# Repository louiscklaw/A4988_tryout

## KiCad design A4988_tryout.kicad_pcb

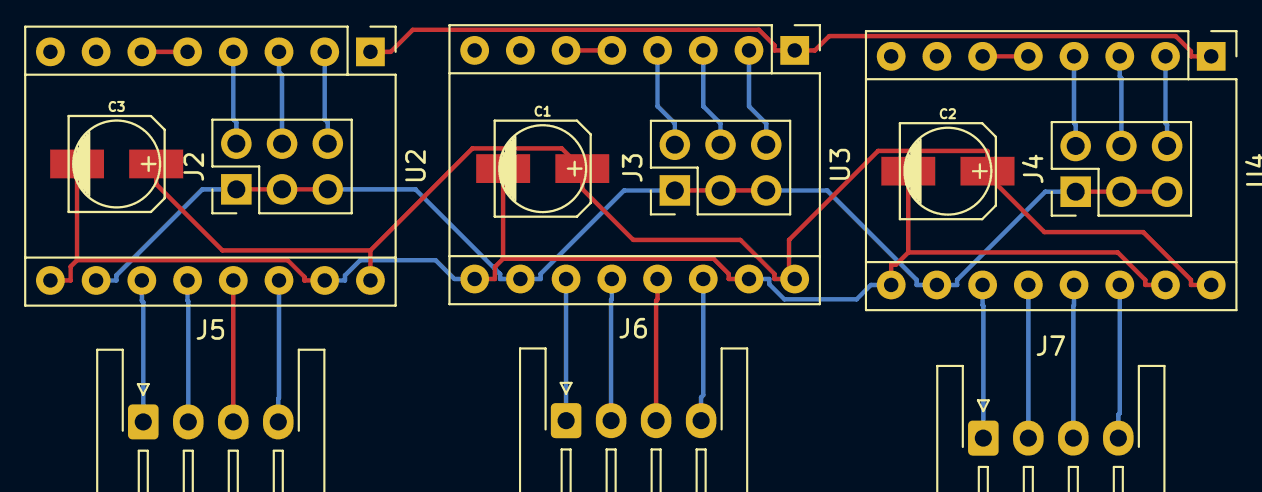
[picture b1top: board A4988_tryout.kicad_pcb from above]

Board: 2 copper layers, 12 parts (0 on the bottom side), 28 nets.

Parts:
C1, C2, C3: CP47uf,35V; c_elec_5x5.3
J2, J3, J4: Conn_02x03_Odd_Even; PinHeader_2x03_P2.54mm_Vertical
J5, J6, J7: Conn_01x04; JST_XH_S04B-XH-A-1_1x04_P2.50mm_Horizontal
U2, U3, U4: A4988_MODULE; Pololu_Breakout-16_15.2x20.3mm

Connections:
+5V: J2.1, J2.3, J2.5, J3.1, J3.3, J3.5, J4.1, J4.3, J4.5, U2.10, U3.10, U4.10
+VMot: C1.1, C2.1, C3.1, U2.16, U3.16, U4.16
GND: C1.2, C2.2, C3.2, U2.9, U2.15, U3.9, U3.15, U4.9, U4.15
unnamed: J2.2, U2.4
unnamed: J2.4, U2.3
unnamed: J2.6, U2.2
unnamed: J3.2, U3.4
unnamed: J3.4, U3.3
unnamed: J3.6, U3.2
unnamed: J4.2, U4.4
unnamed: J4.4, U4.3
unnamed: J4.6, U4.2
unnamed: J5.1, U2.11
unnamed: J5.2, U2.12
unnamed: J5.3, U2.13
unnamed: J5.4, U2.14
unnamed: J6.1, U3.11
unnamed: J6.2, U3.12
unnamed: J6.3, U3.13
unnamed: J6.4, U3.14
unnamed: J7.1, U4.11
unnamed: J7.2, U4.12
unnamed: J7.3, U4.13
unnamed: J7.4, U4.14
unnamed: U2.5, U2.6
unnamed: U3.5, U3.6
unnamed: U4.5, U4.6
Step_Enable: U2.1, U3.1, U4.1

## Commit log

2018-12-04 update,
2020-05-05 ci: init travis build config,
2020-05-05 ci: init travis token,
